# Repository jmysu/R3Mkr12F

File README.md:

# R3Mkr12F
Arduino R3 w/ MKR w/ ESP-12F VaporWare

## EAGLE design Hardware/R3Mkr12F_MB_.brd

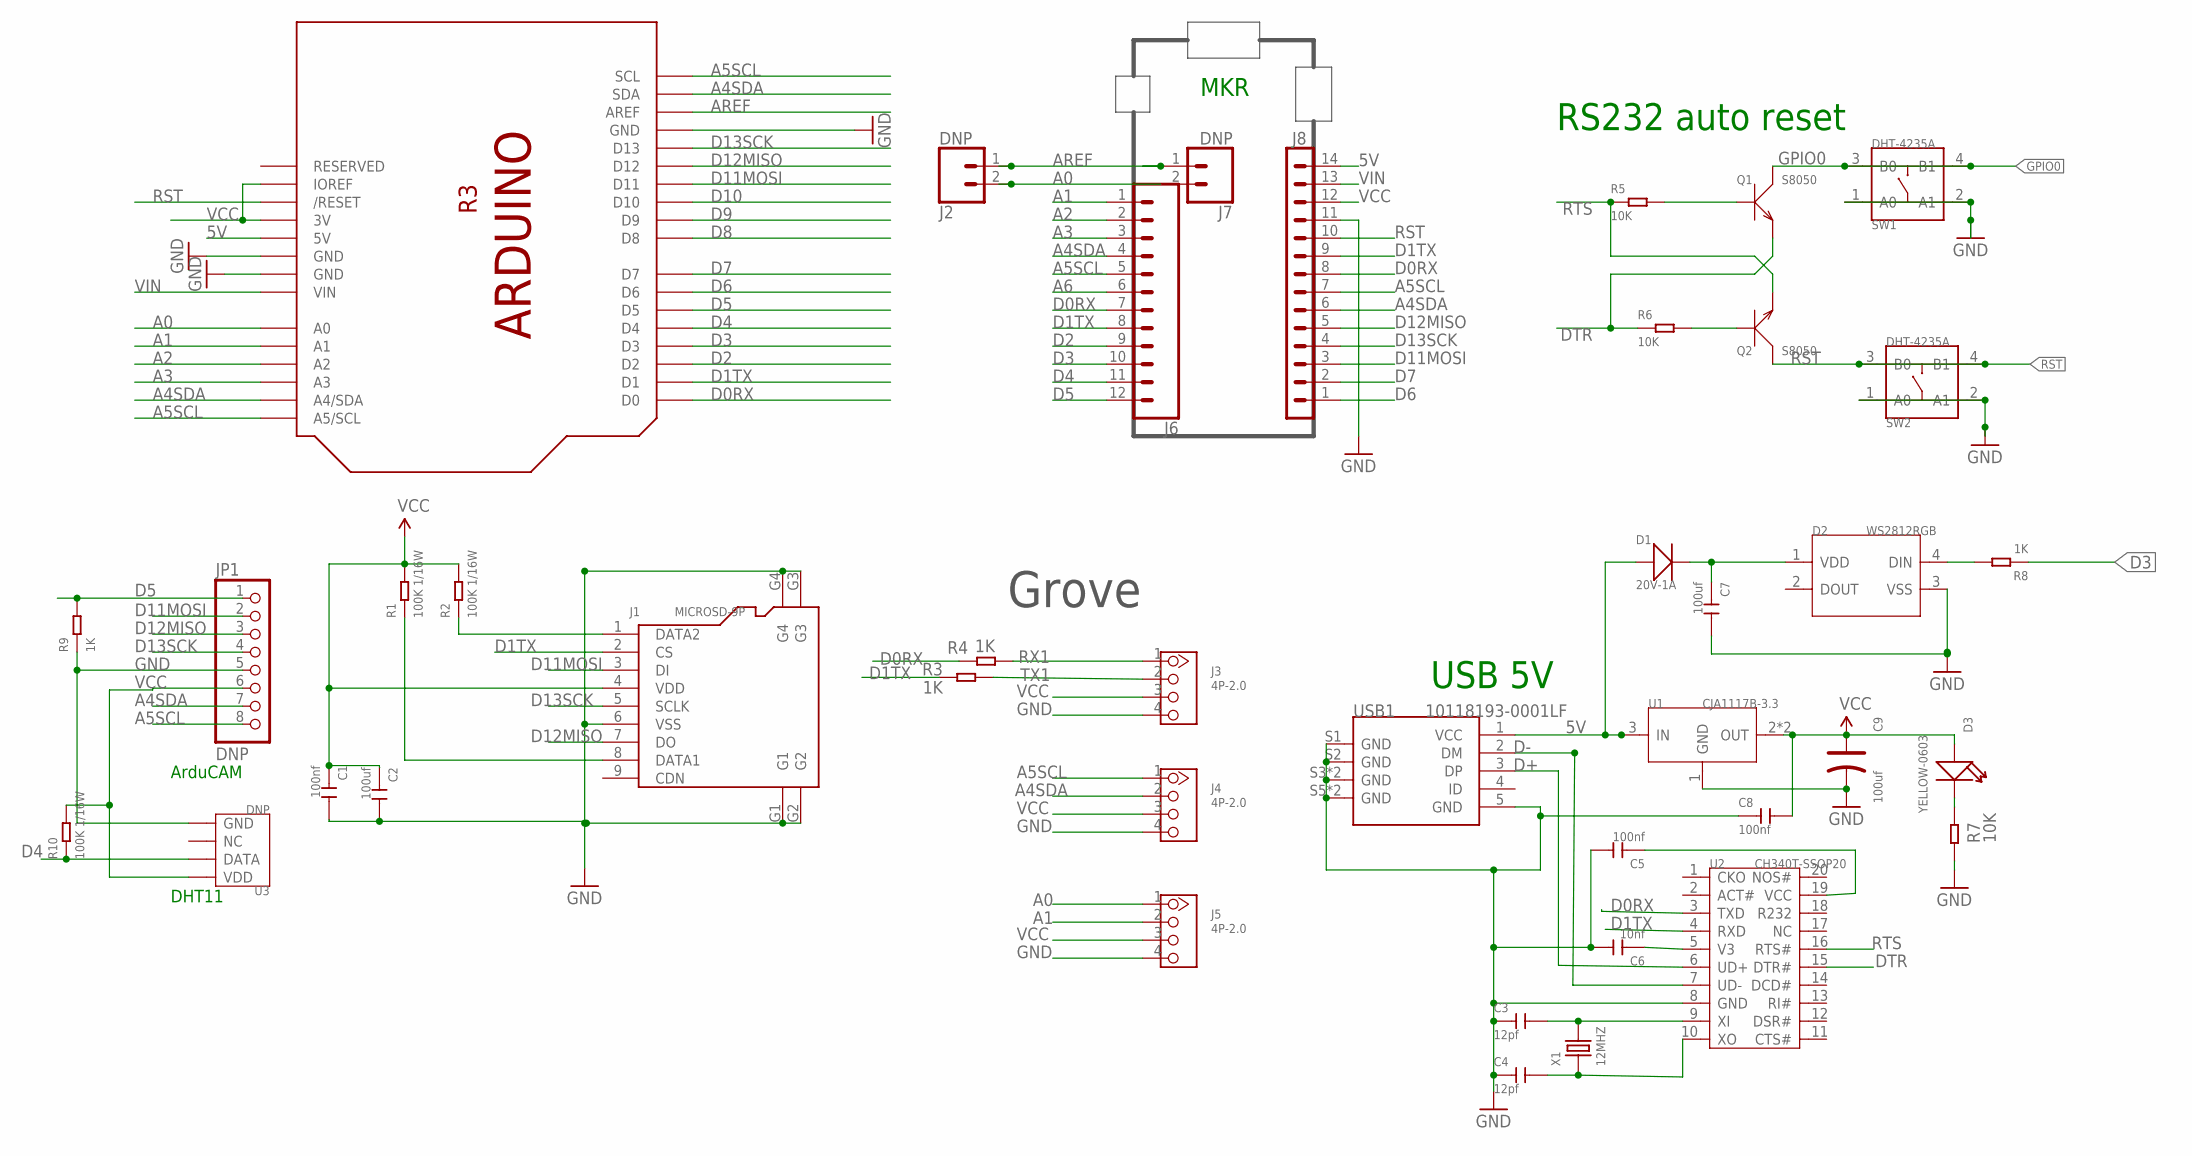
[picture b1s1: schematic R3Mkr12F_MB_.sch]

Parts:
C1, C5, C8: 100nf; C0603
C2, C7: 100uf; C1206
C3, C4: 12pf; C0402
C6: 10nf; C0603
C9: 100uf; AVX-B
D1: 20V-1A; SOD-123
D2: WS2812RGB; LED4-SMD-5050
D3: YELLOW-0603; LED-0603
J1: MICROSD-9P; MICRO-SD9+4P-SMD-16.1X14.5X1.85MM
J2, J7: DNP; 1X02
J3, J4, J5: 4P-2.0; HW4-2.0
J6: CONN_12LOCK; 1X12_LOCK
J8: DNP; 1X14
JP1: DNP; MILLER_1X08-LOCK
Q1, Q2: S8050; SOT-23
R1, R2, R10: 100K 1/16W; R0402
R3, R4, R8, R9: 1K; R0805
R5, R6, R7: 10K; R0402
SW1, SW2: DHT-4235A; SW4-SMD-4.2X3.2X2.5MM
U1: CJA1117B-3.3; SOT-89
U2: CH340T-SSOP20; SSOP20-0.65-7.6X5.2MM
U3: DNP; SNR4-2.54-15.5X12.0X5.5MM
UNO1: ARDUINO_R3_NOICSP_47MM; ARDUINOR3_NOICSP_47MM
USB1: 10118193-0001LF; MICRO-USB5+6P-SMD-0.65-B
X1: 12MHZ; X2-SMD-5.0X3.2X1.3MM

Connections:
5V: D1.+, J8.14, U1.3 (IN), UNO1.5V, USB1.1 (VCC)
A0: J2.2, J5.1, J7.2, UNO1.A0
A1: J5.2, J6.1, UNO1.A1
A2: J6.2, UNO1.A2
A3: J6.3, UNO1.A3
A4SDA: J4.2, J6.4, J8.6, JP1.7, UNO1.A4 (A4/SDA), UNO1.SDA
A5SCL: J4.1, J6.5, J8.7, JP1.8, UNO1.A5 (A5/SCL), UNO1.SCL
A6: J6.6
AREF: J2.1, J7.1, UNO1.AREF
D0RX: J6.7, J8.8, R4.2, U2.3 (TXD), UNO1.D0
D1TX: J1.2 (CS), J6.8, J8.9, R3.2, U2.4 (RXD), UNO1.D1
D2: J6.9, UNO1.D2
D3: J6.10, R8.1, UNO1.D3
D4: J6.11, R10.1, U3.2 (DATA), UNO1.D4
D5: J6.12, JP1.1, R9.2, UNO1.D5
D6: J8.1, UNO1.D6
D7: J8.2, UNO1.D7
D8: UNO1.D8
D9: UNO1.D9
D10: UNO1.D10
D11MOSI: J1.3 (DI), J8.3, JP1.2, UNO1.D11
D12MISO: J1.7 (DO), J8.5, JP1.3, UNO1.D12
D13SCK: J1.5 (SCLK), J8.4, JP1.4, UNO1.D13
D+: U2.6 (UD+), USB1.3 (DP)
D-: U2.7 (UD-), USB1.2 (DM)
DTR: Q1.2 (E), R6.1, U2.15 (DTR#)
GND: C1.2, C2.2, C3.1, C4.1, C5.2, C6.2, C7.2, C8.1, C9.-, D2.3 (VSS), J1.6 (VSS), J1.G1, J1.G2, J1.G3, J1.G4, J3.4, J4.4, J5.4, J8.11, JP1.5, R7.1, R9.1, SW1.1 (A0), SW1.2 (A1), SW2.1 (A0), SW2.2 (A1), U1.1 (GND), U2.8 (GND), U3.4 (GND), UNO1.GND, UNO1.GND@1 (GND), UNO1.GND@2 (GND), USB1.5 (GND), USB1.S1 (GND), USB1.S2 (GND), USB1.S3 (GND), USB1.S4 (GND), USB1.S5 (GND), USB1.S6 (GND)
GPIO0: Q1.3 (C), SW1.3 (B0), SW1.4 (B1)
unnamed: C3.2, U2.9 (XI), X1.2
unnamed: C4.2, U2.10 (XO), X1.1
unnamed: J1.8 (DATA1), R1.1
unnamed: J1.1 (DATA2), R2.1
unnamed: D2.4 (DIN), R8.2
unnamed: Q2.1 (B), R6.2
unnamed: Q1.1 (B), R5.2
unnamed: D3.-, R7.2
RST: J8.10, Q2.3 (C), SW2.3 (B0), SW2.4 (B1), UNO1.RESET (/RESET)
RTS: Q2.2 (E), R5.1, U2.16 (RTS#)
RX1: J3.1, R4.1
TX1: J3.2, R3.1
V1: C7.1, D1.-, D2.1 (VDD)
V3: C6.1, U2.5 (V3)
VCC: C1.1, C2.1, C5.1, C8.2, C9.+, D3.+, J1.4 (VDD), J3.3, J4.3, J5.3, J8.12, JP1.6, R1.2, R2.2, R10.2, U1.2 (OUT), U1.4 (OUT), U2.19 (VCC), U3.1 (VDD), UNO1.3V, UNO1.IOREF
VIN: J8.13, UNO1.VIN

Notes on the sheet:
Grove
USB 5V
RS232 auto reset
DHT11
ArduCAM
MKR

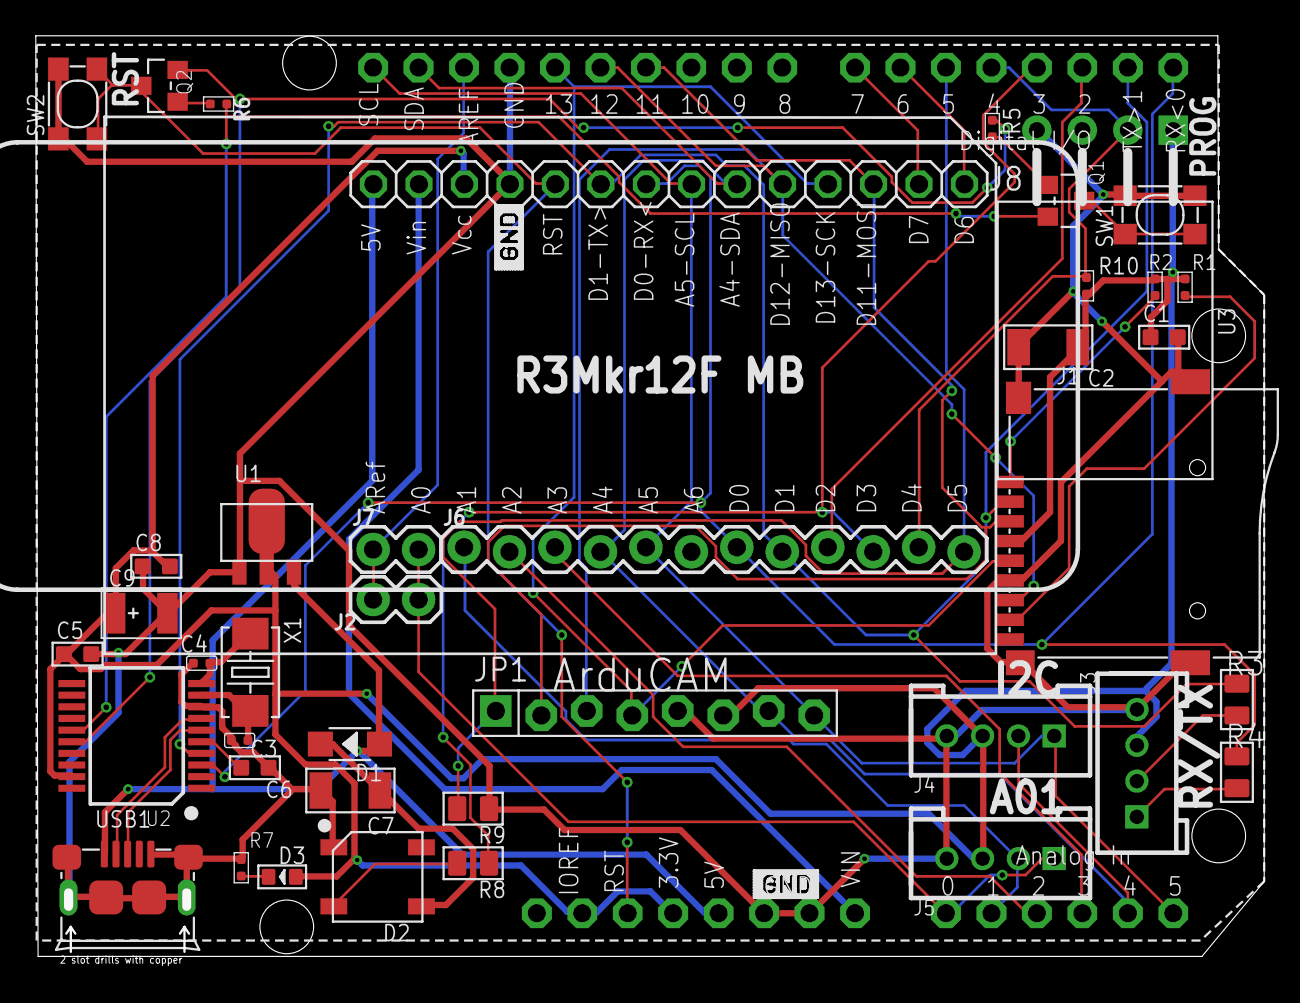
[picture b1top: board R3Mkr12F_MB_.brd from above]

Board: 2 copper layers, 68.1 x 51.6 mm, 41 parts (0 on the bottom side), 40 nets.

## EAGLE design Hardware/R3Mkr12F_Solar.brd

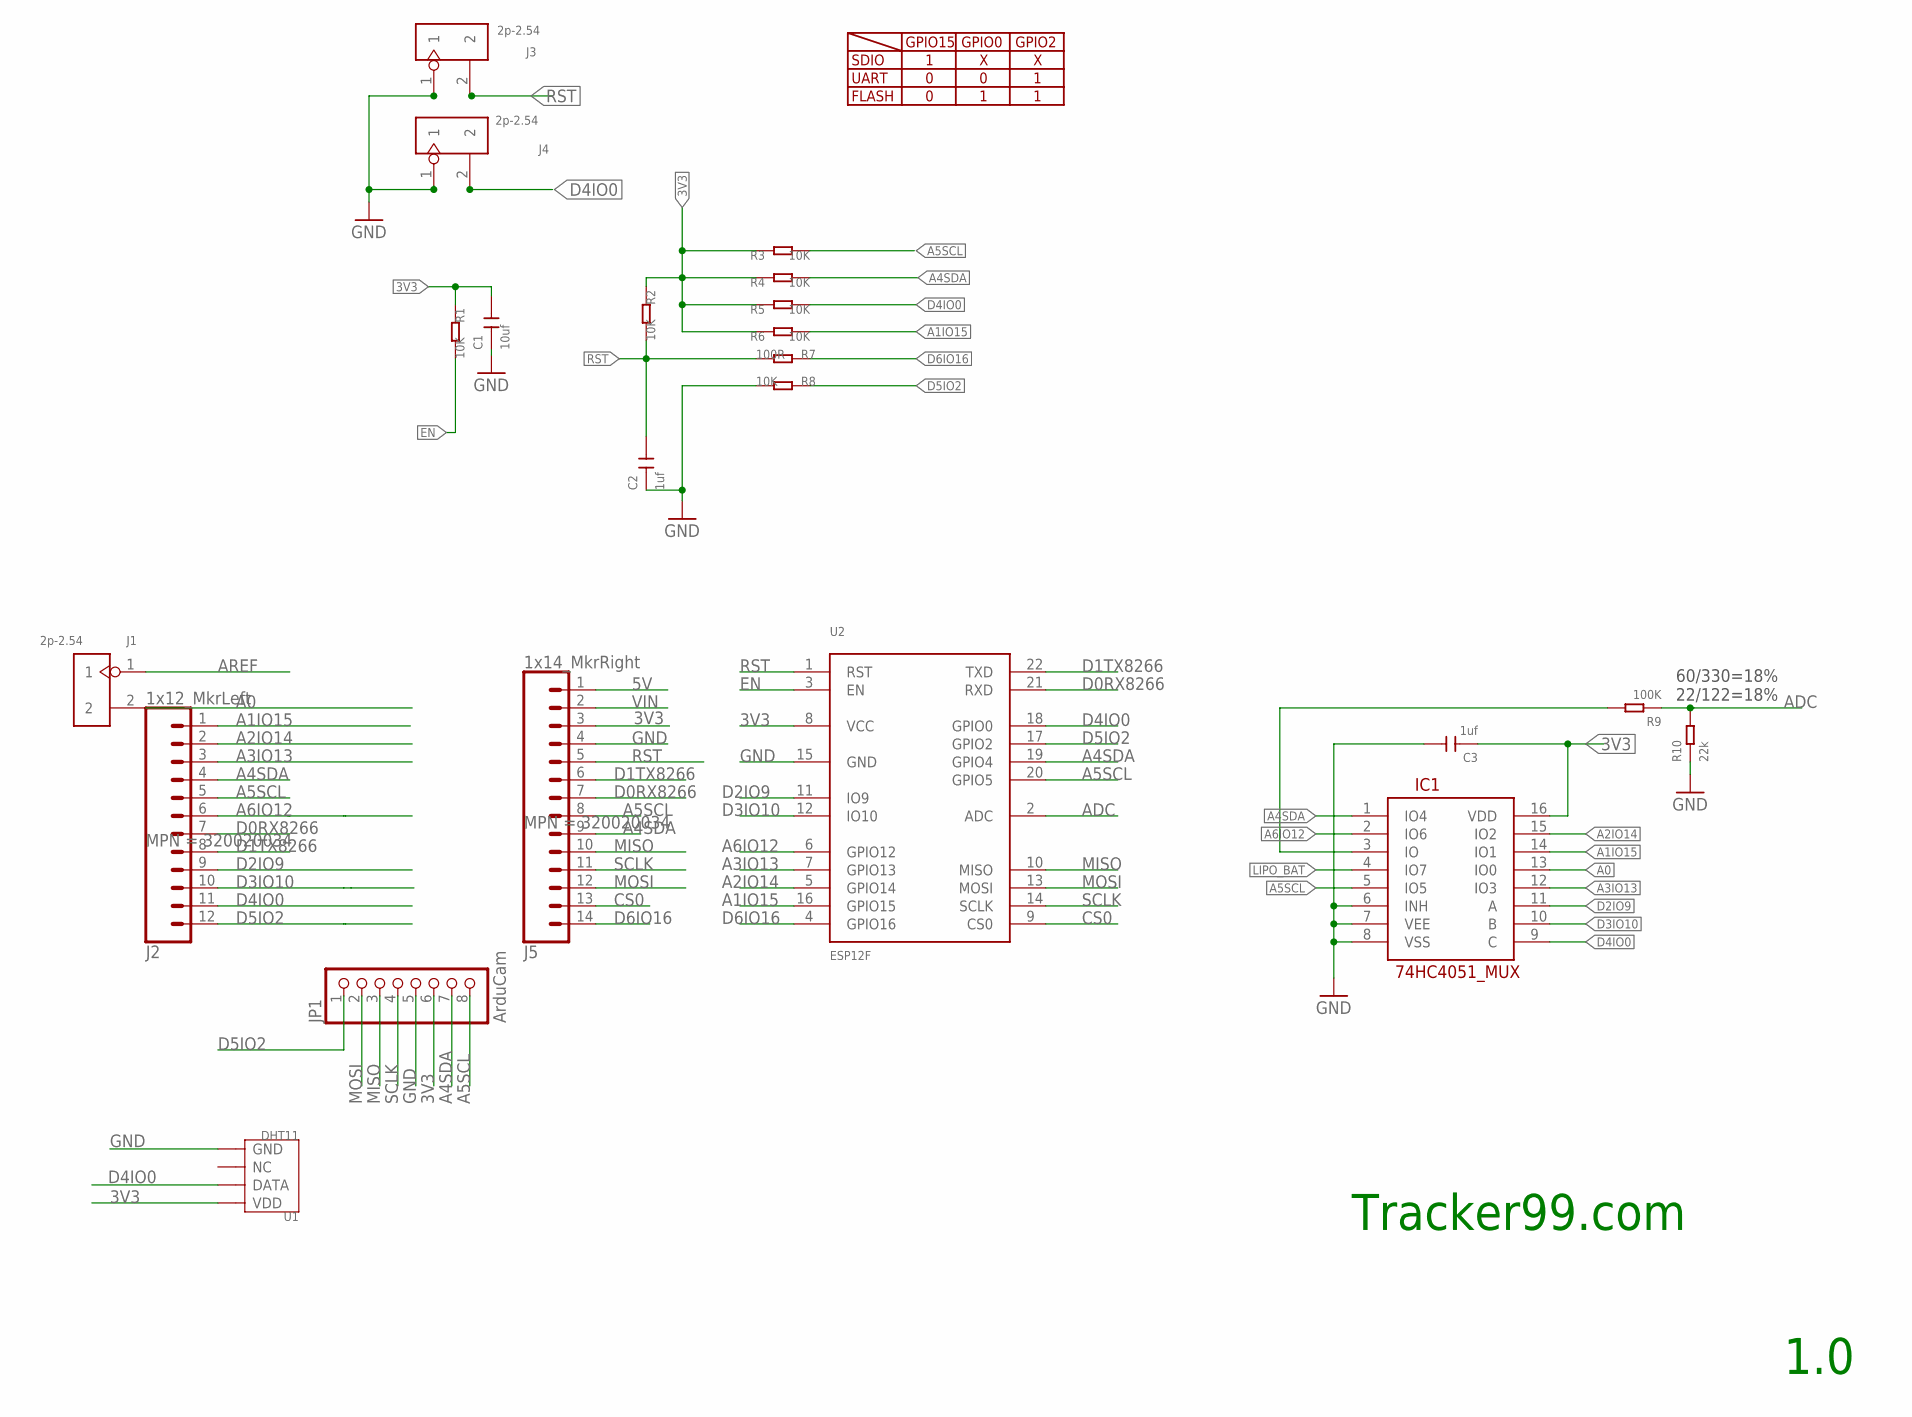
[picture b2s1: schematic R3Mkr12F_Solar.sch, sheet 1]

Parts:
C1: 10uf; C0603
C2, C3: 1uf; C0603
IC1: 74HC4051_MUX; SPARKFUN_SO16
J1, J3, J4: 2p-2.54; H2-2.54
J2: 1x12_MkrLeft; 1X12_LOCK; MPN 320020034
J5: 1x14_MkrRight; 1X14_LOCK; MPN 320020034
JP1: ArduCam; MILLER_1X08-LOCK
R1, R2, R3, R4, R5, R6, R8: 10K; SEEED-RESISTOR_R0402
R7: 100R; R0603
R9: 100K; R0402
R10: 22k; R0402
U1: DHT11; SNR4-2.54-15.5X12.0X5.5MM
U2: ESP12F; ESP-12F

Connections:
3V3: C1.2, C3.1, IC1.16 (VDD), J5.3, JP1.6, R1.1, R2.1, R3.1, R4.1, R5.1, R6.1, U1.1 (VDD), U2.8 (VCC); also elsewhere on the board
5V: J5.1; also elsewhere on the board
A0: IC1.13 (IO0), J1.2
A1IO15: IC1.14 (IO1), J2.1, R6.2, U2.16 (GPIO15)
A2IO14: IC1.15 (IO2), J2.2, U2.5 (GPIO14)
A3IO13: IC1.12 (IO3), J2.3, U2.7 (GPIO13)
A4SDA: IC1.1 (IO4), J2.4, J5.9, JP1.7, R4.2, U2.19 (GPIO4)
A5SCL: IC1.5 (IO5), J2.5, J5.8, JP1.8, R3.2, U2.20 (GPIO5)
A6IO12: IC1.2 (IO6), J2.6, U2.6 (GPIO12)
ADC: R9.1, R10.2, U2.2 (ADC)
AREF: J1.1
CS0: J5.13, U2.9 (CS0)
D0RX8266: J2.7, J5.7, U2.21 (RXD)
D1TX8266: J2.8, J5.6, U2.22 (TXD)
D2IO9: IC1.11 (A), J2.9, U2.11 (IO9)
D3IO10: IC1.10 (B), J2.10, U2.12 (IO10)
D4IO0: IC1.9 (C), J2.11, J4.2, R5.2, U1.2 (DATA), U2.18 (GPIO0)
D5IO2: J2.12, JP1.1, R8.1, U2.17 (GPIO2)
D6IO16: J5.14, R7.1, U2.4 (GPIO16)
EN: R1.2, U2.3 (EN)
GND: C1.1, C2.1, C3.2, IC1.6 (INH), IC1.7 (VEE), IC1.8 (VSS), J3.1, J4.1, J5.4, JP1.5, R8.2, R10.1, U1.4 (GND), U2.15 (GND); also elsewhere on the board
LIPO_BAT: IC1.4 (IO7); also elsewhere on the board
MISO: J5.10, JP1.3, U2.10 (MISO)
MOSI: J5.12, JP1.2, U2.13 (MOSI)
RST: C2.2, J3.2, J5.5, R2.2, R7.2, U2.1 (RST)
SCLK: J5.11, JP1.4, U2.14 (SCLK)
VIN: J5.2
Z: IC1.3 (IO), R9.2

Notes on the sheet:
SDIO
UART
FLASH
GPIO15
GPIO0
GPIO2
60/330=18% 22/122=18%
Tracker99.com
1.0

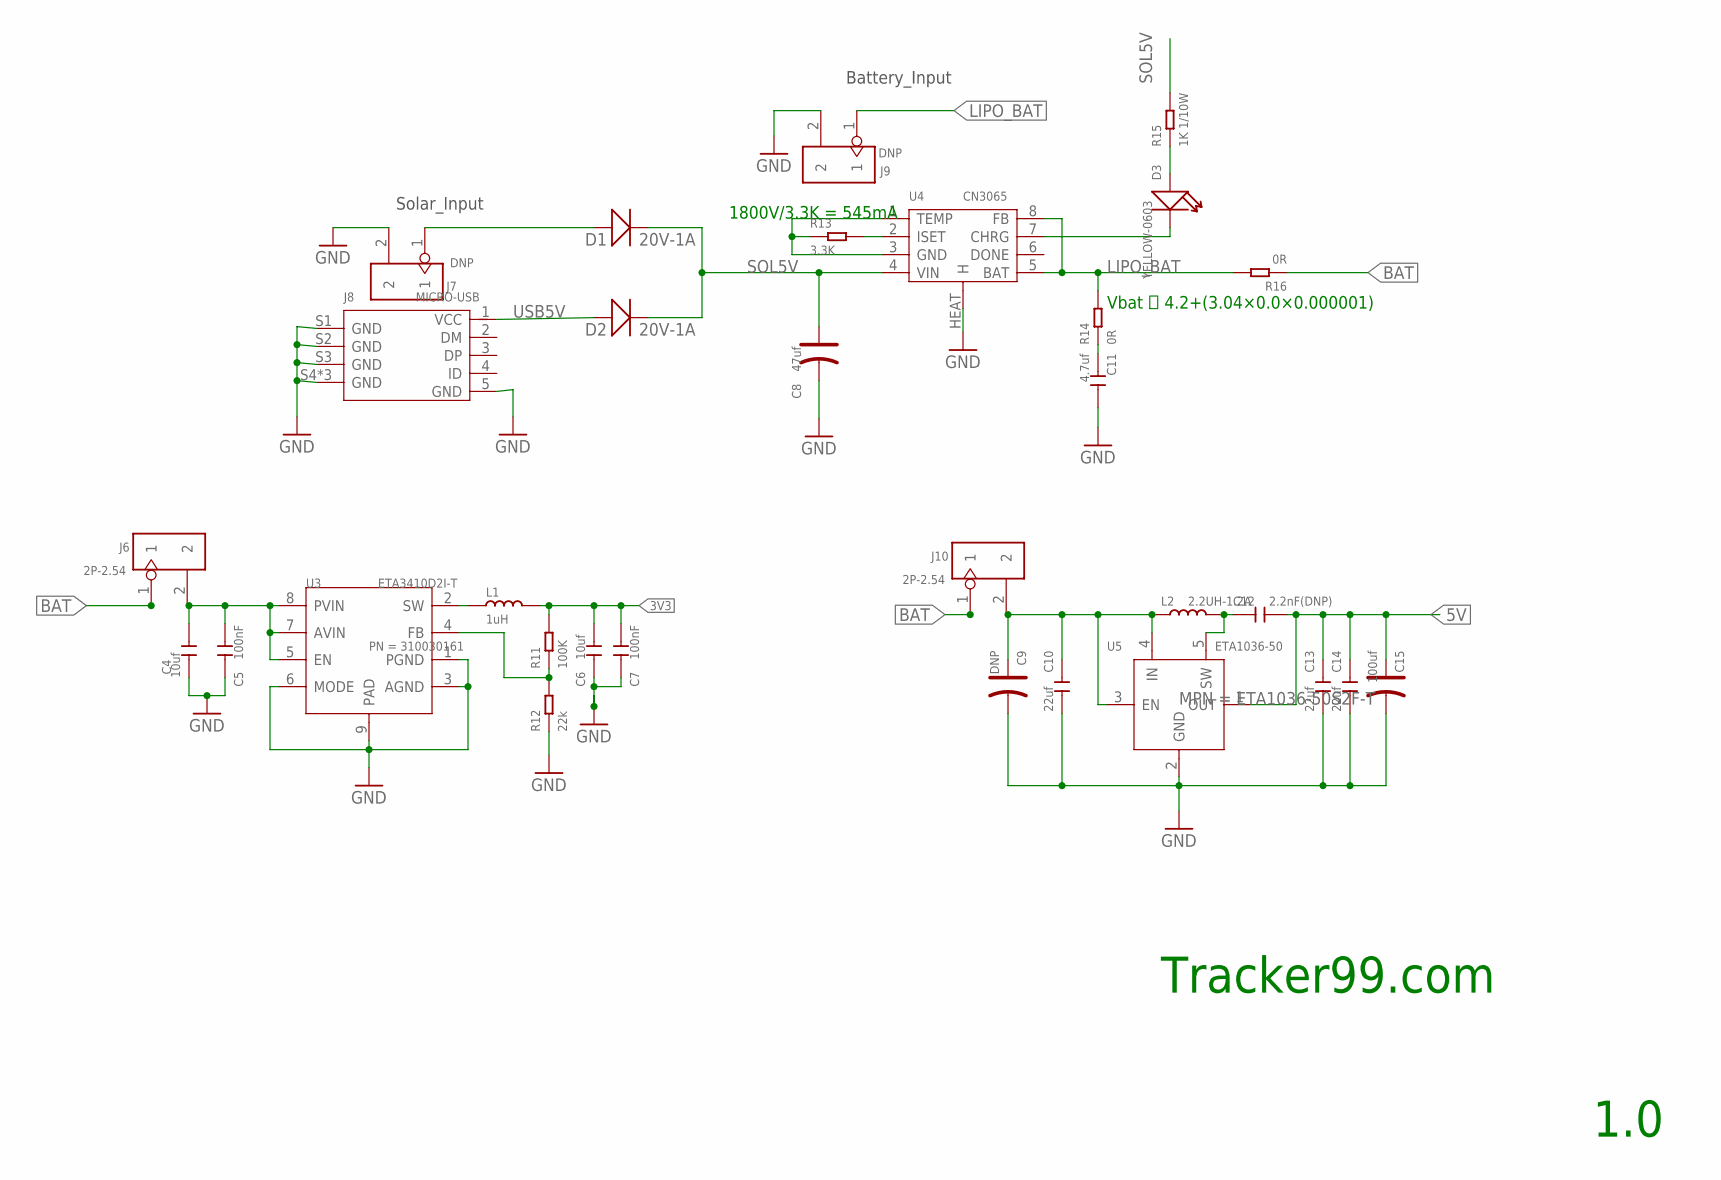
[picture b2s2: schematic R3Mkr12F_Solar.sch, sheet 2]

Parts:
C4, C6: 10uf; C0805
C5, C7: 100nF; C0402
C8: 47uf; AVX-A
C9: DNP; AVX-B
C10, C13, C14: 22uf; C0805
C11: 4.7uf; C0603
C12: 2.2nF(DNP); C0603
C15: 100uf; AVX-B
D1, D2: 20V-1A; SOD-123
D3: YELLOW-0603; LED-0603
J6, J10: 2P-2.54; H2-2.54
J7, J9: DNP; H2-2.54
J8: MICRO-USB; MICRO-USB5+4P-SMD-0.65-B
L1: 1uH; L0603
L2: 2.2UH-1.2A; L0805
R11: 100K; R0402
R12: 22k; R0402
R13: 3.3K; R0603
R14, R16: 0R; R0603
R15: 1K 1/10W; R0603
U3: ETA3410D2I-T; DFN8G-0.5-2X2MM
U4: CN3065; DFN-8
U5: ETA1036-50; SOT23-5; MPN ETA1036-50S2F-T

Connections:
3V3: C6.2, C7.2, L1.2, R11.2; also elsewhere on the board
5V: C12.2, C13.1, C14.1, C15.+, U5.1 (OUT); also elsewhere on the board
BAT: J6.1, J10.1, R16.1
BAT_3V3_IN: C4.2, C5.2, J6.2, U3.5 (EN), U3.7 (AVIN), U3.8 (PVIN)
BAT_IN: C9.+, C10.1, J10.2, L2.1, U5.3 (EN), U5.4 (IN)
GND: C4.1, C5.1, C6.1, C7.1, C8.-, C9.-, C10.2, C11.2, C13.2, C14.2, C15.-, J7.2, J8.5 (GND), J8.S1 (GND), J8.S2 (GND), J8.S3 (GND), J8.S4 (GND), J8.S5 (GND), J8.S6 (GND), J9.2, R12.1, R13.1, U3.1 (PGND), U3.3 (AGND), U3.6 (MODE), U3.9 (PAD), U4.1 (TEMP), U4.3 (GND), U4.HEAT (H), U5.2 (GND); also elsewhere on the board
LIPO_BAT: J9.1, R14.2, R16.2, U4.5 (BAT), U4.8 (FB); also elsewhere on the board
unnamed: D1.+, J7.1
unnamed: D3.+, R15.1
unnamed: L1.1, U3.2 (SW)
unnamed: R11.1, R12.2, U3.4 (FB)
unnamed: R13.2, U4.2 (ISET)
unnamed: D3.-, U4.7 (CHRG)
unnamed: C11.1, R14.1
unnamed: C12.1, L2.2, U5.5 (SW)
SOL5V: C8.+, D1.-, D2.-, R15.2, U4.4 (VIN)
USB5V: D2.+, J8.1 (VCC)

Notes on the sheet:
Solar_Input
Battery_Input
Vbat ＝ 4.2+(3.04×0.0×0.000001)
1800V/3.3K = 545mA
Tracker99.com
1.0

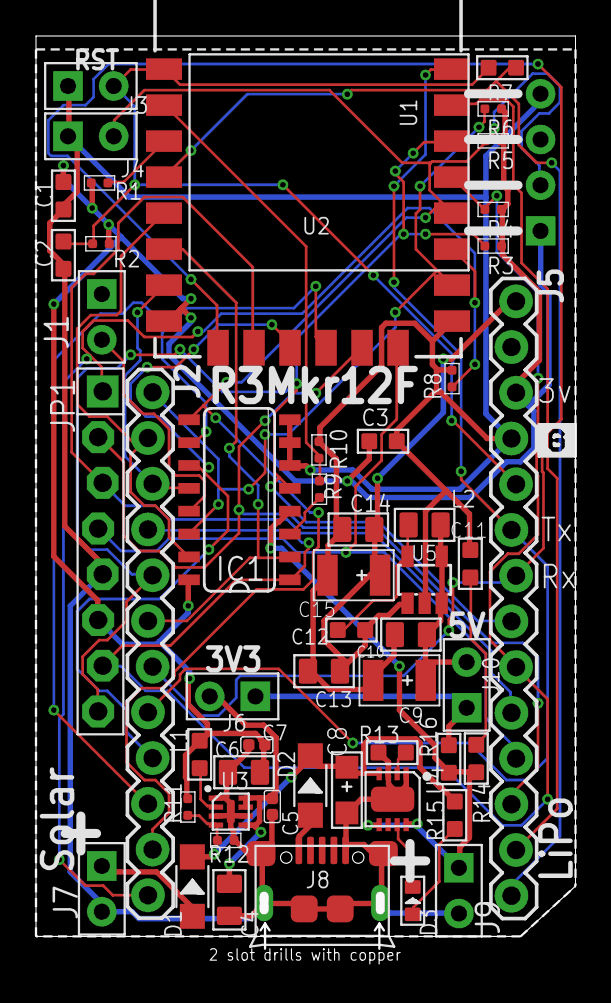
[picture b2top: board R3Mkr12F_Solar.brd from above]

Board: 2 copper layers, 29.5 x 51.2 mm, 53 parts (0 on the bottom side), 39 nets.

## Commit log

2019-06-03 Create Hardware

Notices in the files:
parts and their libraries:
SparkFun-Connectors: Licensing: Creative Commons ShareAlike 4.0 International - https://creativecommons.org/licenses/by-sa/4.0
